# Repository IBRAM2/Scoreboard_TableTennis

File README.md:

# Tennis Scoreboard

## Simulation
The software used to perform the circuit simulations is proteus, this software its not free, so I provide a "student" version below.

Download Link: [Proteus Student Version](https://drive.google.com/drive/folders/1Nruetk5m6KCmWx57GLWE98xntiZ9FSeq?usp=drive_link)

### Installation Instructions

You need Windows OS to install proteus
1. Install the .exe, the default ***installation_path*** is: 
    > C:\Program Files (x86)\Labcenter Electronics\Proteus 8 Professional

2. On ***installation_path***/DATA/LIBRARY paste the contents of **"librerias-arduino"**

3. (Optional) On ***installation_path*** remplace Translations directory with the content of **"Paquete de idiomas"**.

### Run Simulation
1. Open **Arduino IDE**, go to File, preferences, and select verbose on compilation.

2. Compile the program, Towards the end of the terminal output, you will be able to see the path where the program was compiled
    > C:\\Users\\name\\AppData\\Local\\Temp\\arduino-sketch-38788937E004AF96E05C05CDE8CDFB3A\Scoreboard.ino.elf
    >
    Copy the path from the terminal or locate the indicated path, remember that the separators are \ and remove the " at the beginning and end.

3. Open the simulation, and double click on arduino nano, paste the path of the file .elf or .hex on **Program File:**

4. Run the simulatior by clicking on the play symbol in the bottom left corner.

*Note: Due to Arduino compiling the program into temporary files, it's possible that program execution may modify the path. However, this usually doesn't happen within the same session unless you restart the computer.*

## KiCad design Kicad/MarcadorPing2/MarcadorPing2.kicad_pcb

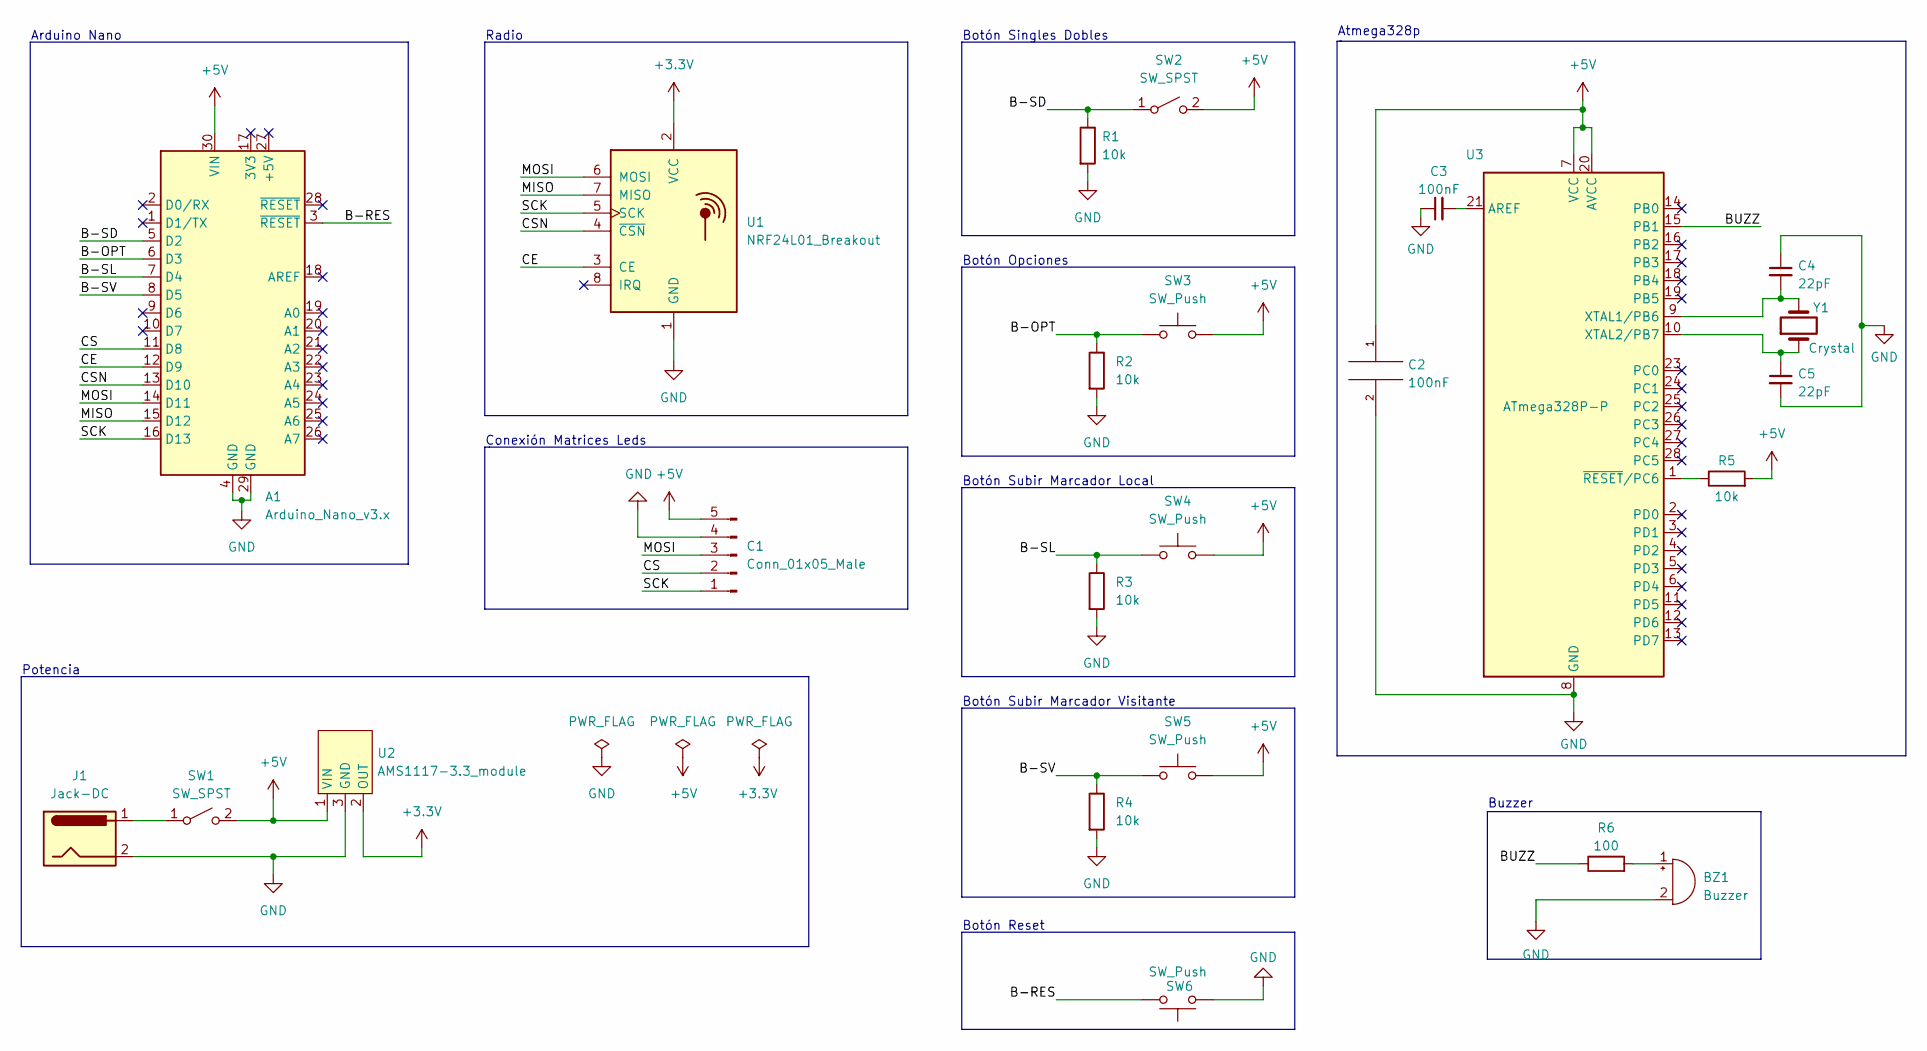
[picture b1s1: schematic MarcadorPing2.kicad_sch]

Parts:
A1: Arduino_Nano_v3.x; Arduino_Nano
BZ1: Buzzer; TerminalBlock_Phoenix_MKDS-1,5-2_1x02_P5.00mm_Horizontal
C1: Conn_01x05_Male; PinHeader_1x05_P2.54mm_Vertical
C2, C3: 100nF; C_Disc_D3.8mm_W2.6mm_P2.50mm
C4, C5: 22pF; C_1206_3216Metric_Pad1.33x1.80mm_HandSolder
J1: Jack-DC; BarrelJack_Horizontal
R1, R2, R3, R4, R5: 10k; R_Axial_DIN0207_L6.3mm_D2.5mm_P7.62mm_Horizontal
R6: 100; R_Axial_DIN0207_L6.3mm_D2.5mm_P7.62mm_Horizontal
SW1, SW2: SW_SPST; TerminalBlock_Phoenix_MKDS-1,5-2_1x02_P5.00mm_Horizontal
SW3, SW4, SW5, SW6: SW_Push; TerminalBlock_Phoenix_MKDS-1,5-2_1x02_P5.00mm_Horizontal
U1: NRF24L01_Breakout; NRF24L01
U2: AMS1117-3.3_module; AMS1117
U3: ATmega328P-P; DIP-28_W7.62mm
Y1: Crystal; Resonator-2Pin_W8.0mm_H3.5mm

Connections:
+3.3V: U1.2 (VCC), U2.2 (OUT)
+5V: A1.30 (VIN), C1.5, C2.1, R5.2, SW1.2 (B), SW2.2 (B), SW3.2, SW4.2, SW5.2, U2.1 (VIN), U3.7 (VCC), U3.20 (AVCC)
/B-OPT: A1.6 (D3), R2.1, SW3.1
/B-RES: A1.3 (~RESET), SW6.2
/B-SD: A1.5 (D2), R1.1, SW2.1 (A)
/B-SL: A1.7 (D4), R3.1, SW4.1
/B-SV: A1.8 (D5), R4.1, SW5.1
/BUZZ: R6.1, U3.15 (PB1)
/CE: A1.12 (D9), U1.3 (CE)
/CS: A1.11 (D8), C1.2
/CSN: A1.13 (D10), U1.4 (~CSN)
/MISO: A1.15 (D12), U1.7 (MISO)
/MOSI: A1.14 (D11), C1.3, U1.6 (MOSI)
/SCK: A1.16 (D13), C1.1, U1.5 (SCK)
GND: A1.4 (GND), A1.29 (GND), BZ1.2 (+), C1.4, C2.2, C3.1, C4.1, C5.2, J1.2, R1.2, R2.2, R3.2, R4.2, SW6.1, U1.1 (GND), U2.3 (GND), U3.8 (GND), U3.22 (GND)
unnamed: BZ1.1 (-), R6.2
unnamed: J1.1, SW1.1 (A)
unnamed: C3.2, U3.21 (AREF)
unnamed: C4.2, U3.9 (XTAL1/PB6), Y1.2
unnamed: C5.1, U3.10 (XTAL2/PB7), Y1.1
unnamed: R5.1, U3.1 (~RESET/PC6)

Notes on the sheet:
Radio
Conexión Matrices Leds
Buzzer
Botón Subir Marcador Local
Botón Opciones
Botón Subir Marcador Visitante
Atmega328p
Potencia
Arduino Nano
Botón Reset
Botón Singles Dobles

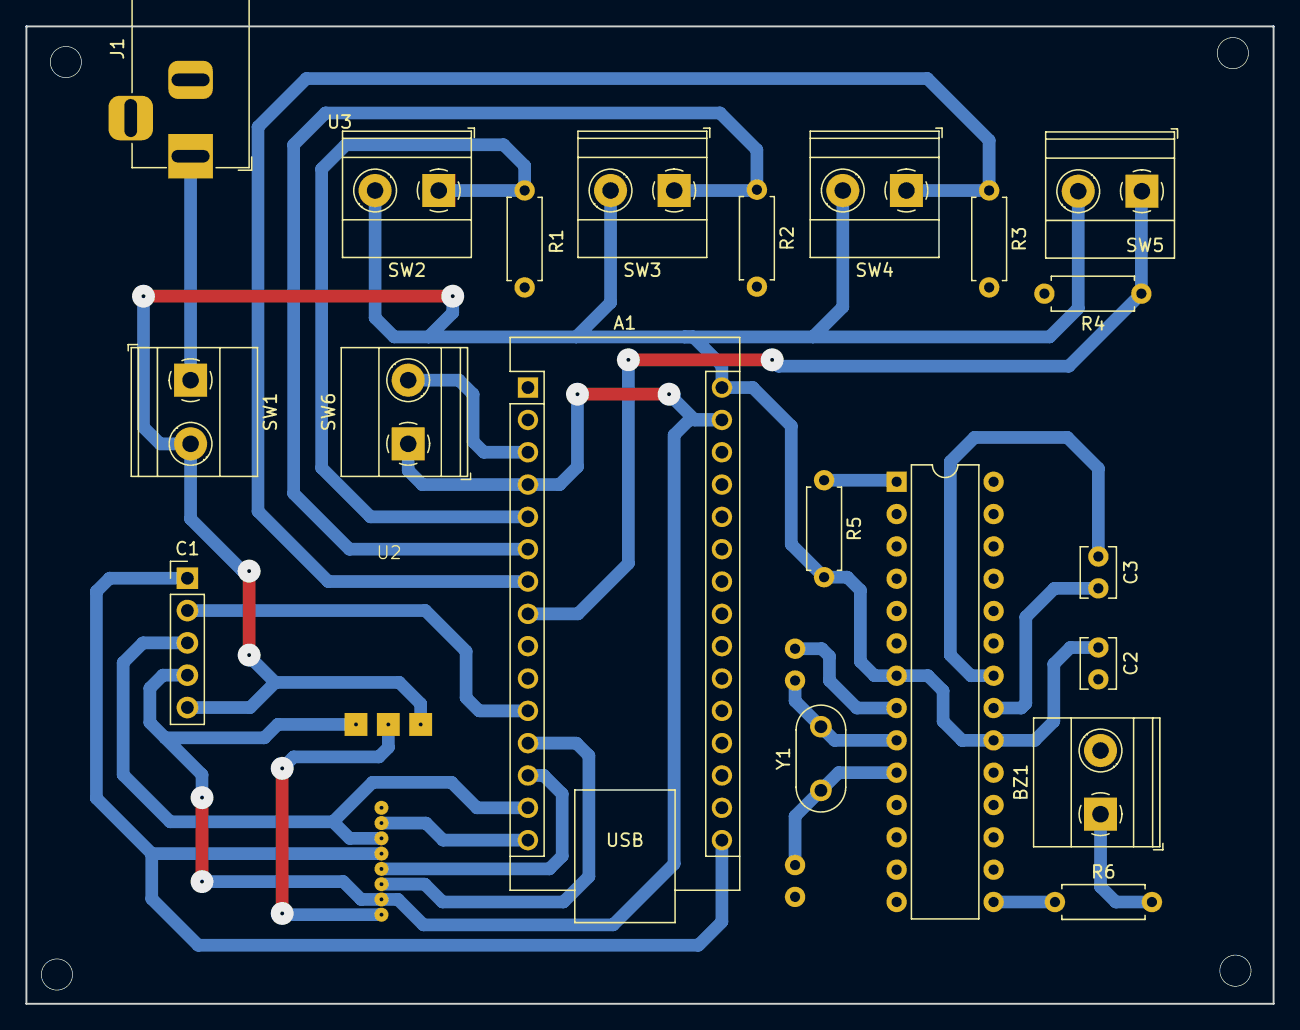
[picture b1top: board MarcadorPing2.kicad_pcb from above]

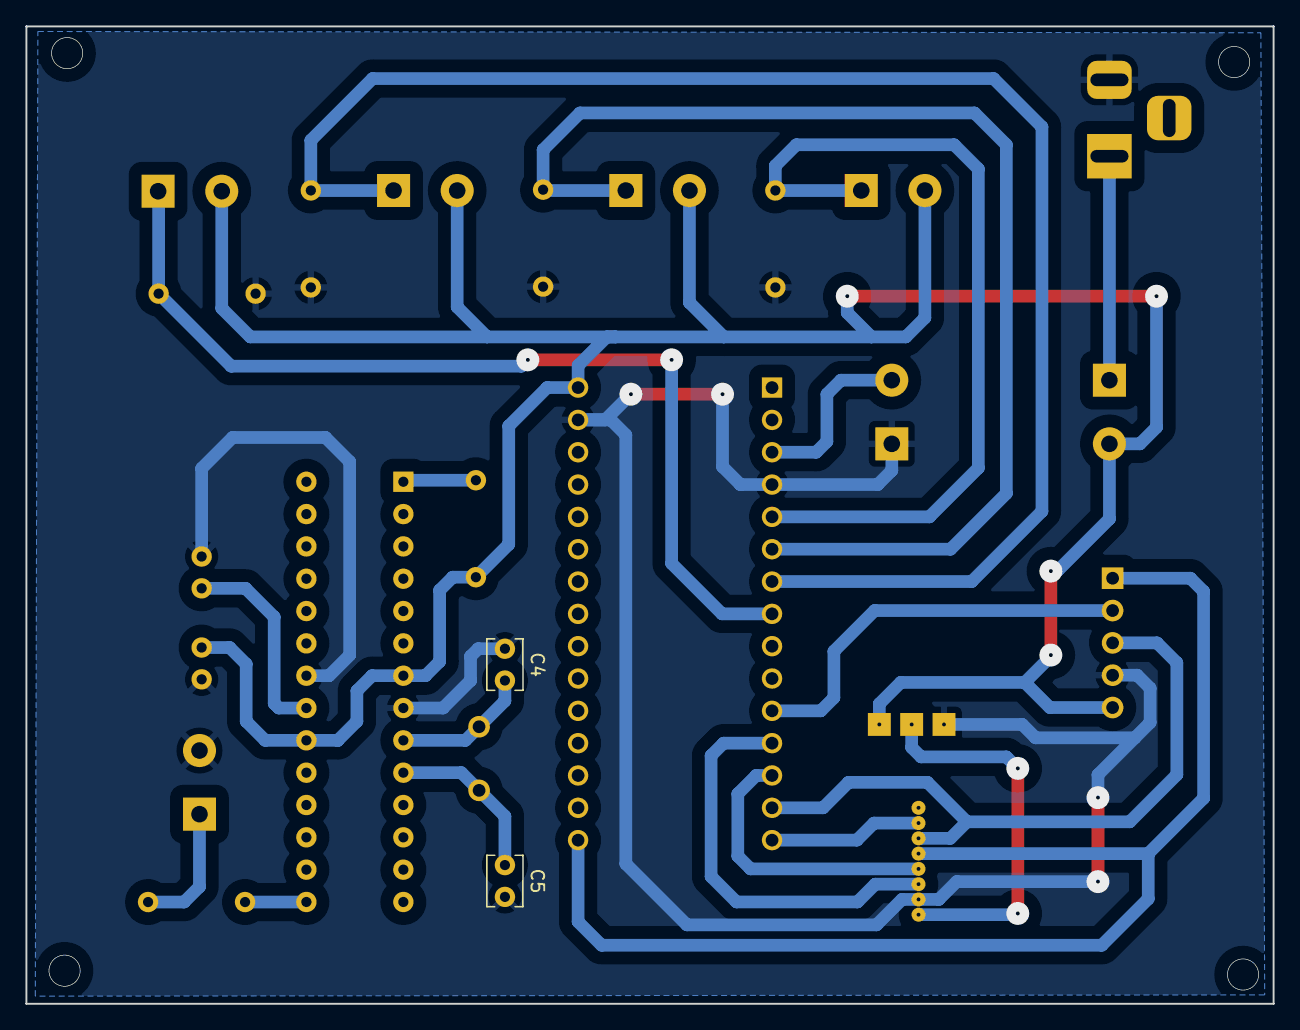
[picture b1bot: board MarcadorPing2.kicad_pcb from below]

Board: 2 copper layers, 98.0 x 76.8 mm, 24 parts (2 on the bottom side), 21 nets.

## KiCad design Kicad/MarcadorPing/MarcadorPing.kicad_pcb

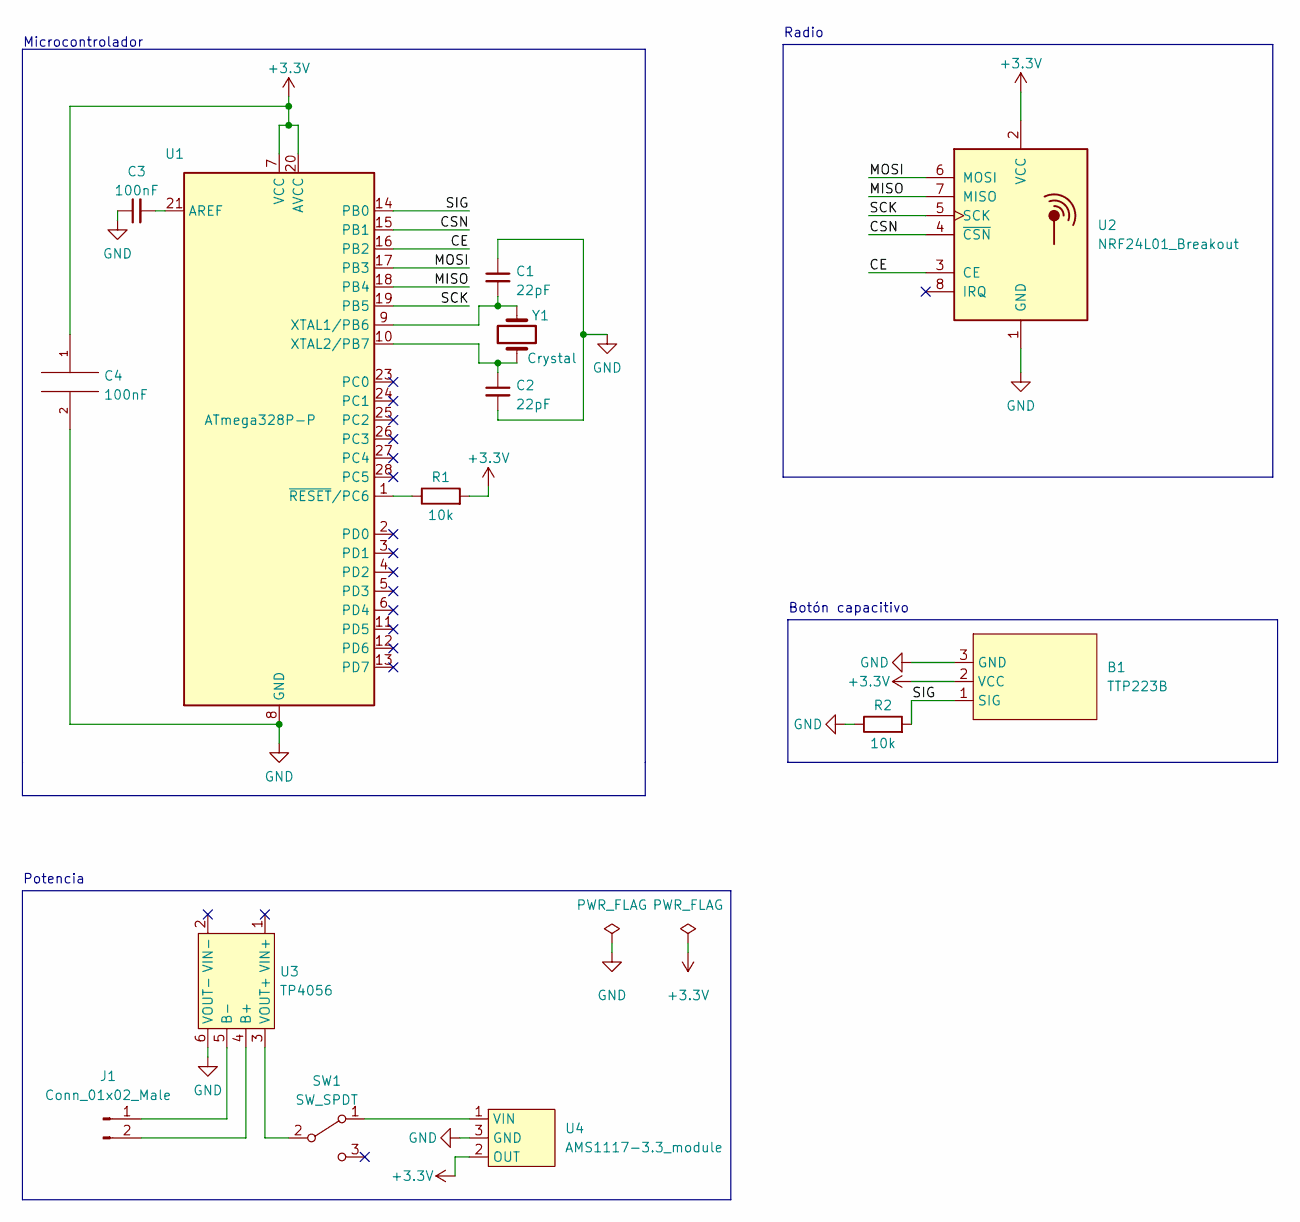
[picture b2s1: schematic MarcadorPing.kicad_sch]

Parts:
B1: TTP223B
C1, C2: 22pF; C_1206_3216Metric_Pad1.33x1.80mm_HandSolder
C3, C4: 100nF; C_Disc_D3.8mm_W2.6mm_P2.50mm
J1: Conn_01x02_Male; LiPo 502030
R1, R2: 10k; R_Axial_DIN0207_L6.3mm_D2.5mm_P7.62mm_Horizontal
SW1: SW_SPDT; PinHeader_1x03_P2.54mm_Vertical
U1: ATmega328P-P; DIP-28_W7.62mm
U2: NRF24L01_Breakout; NRF24L01
U3: TP4056
U4: AMS1117-3.3_module; AMS1117
Y1: Crystal; Resonator-2Pin_W8.0mm_H3.5mm

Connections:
+3.3V: B1.2 (VCC), C4.1, R1.2, U1.7 (VCC), U1.20 (AVCC), U2.2 (VCC), U4.2 (OUT)
/CE: U1.16 (PB2), U2.3 (CE)
/CSN: U1.15 (PB1), U2.4 (~CSN)
/MISO: U1.18 (PB4), U2.7 (MISO)
/MOSI: U1.17 (PB3), U2.6 (MOSI)
/SCK: U1.19 (PB5), U2.5 (SCK)
/SIG: B1.1 (SIG), R2.2, U1.14 (PB0)
GND: B1.3 (GND), C1.1, C2.2, C3.1, C4.2, R2.1, U1.8 (GND), U1.22 (GND), U2.1 (GND), U3.6 (VOUT-), U4.3 (GND)
unnamed: J1.1, U3.5 (B-)
unnamed: J1.2, U3.4 (B+)
unnamed: SW1.1 (A), U4.1 (VIN)
unnamed: SW1.2 (B), U3.3 (VOUT+)
unnamed: C3.2, U1.21 (AREF)
unnamed: C1.2, U1.9 (XTAL1/PB6), Y1.2
unnamed: C2.1, U1.10 (XTAL2/PB7), Y1.1
unnamed: R1.1, U1.1 (~RESET/PC6)

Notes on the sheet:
Radio
Botón capacitivo
Microcontrolador
Potencia

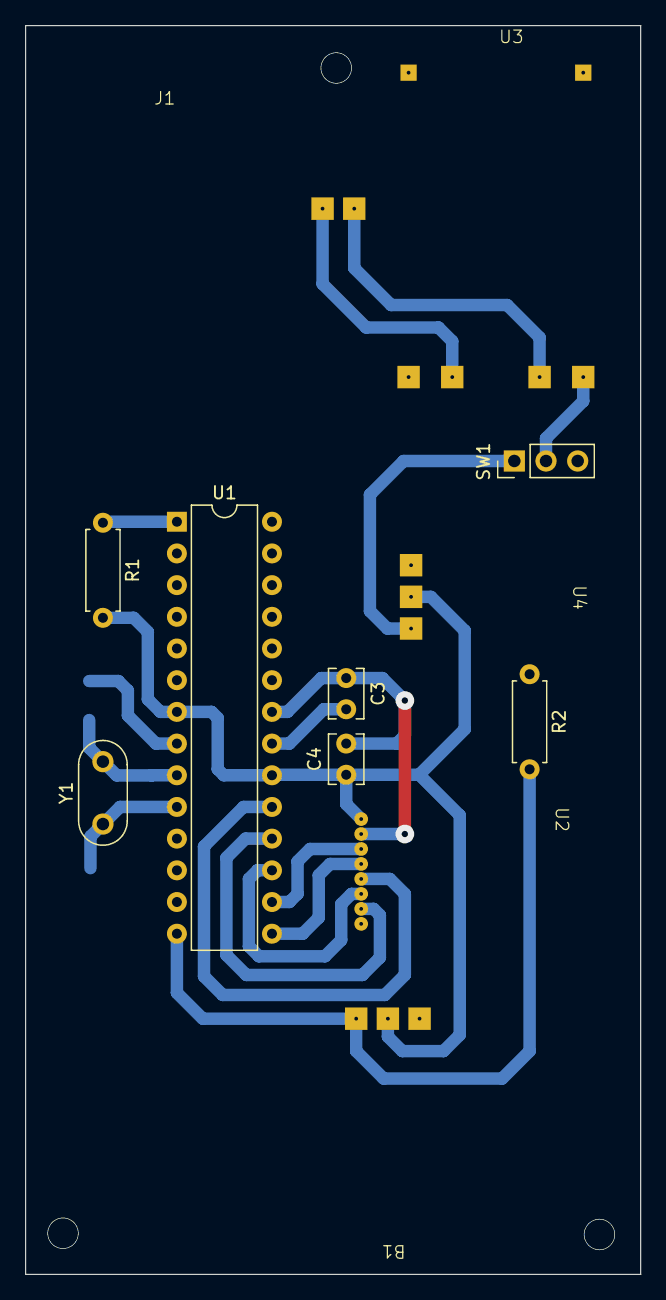
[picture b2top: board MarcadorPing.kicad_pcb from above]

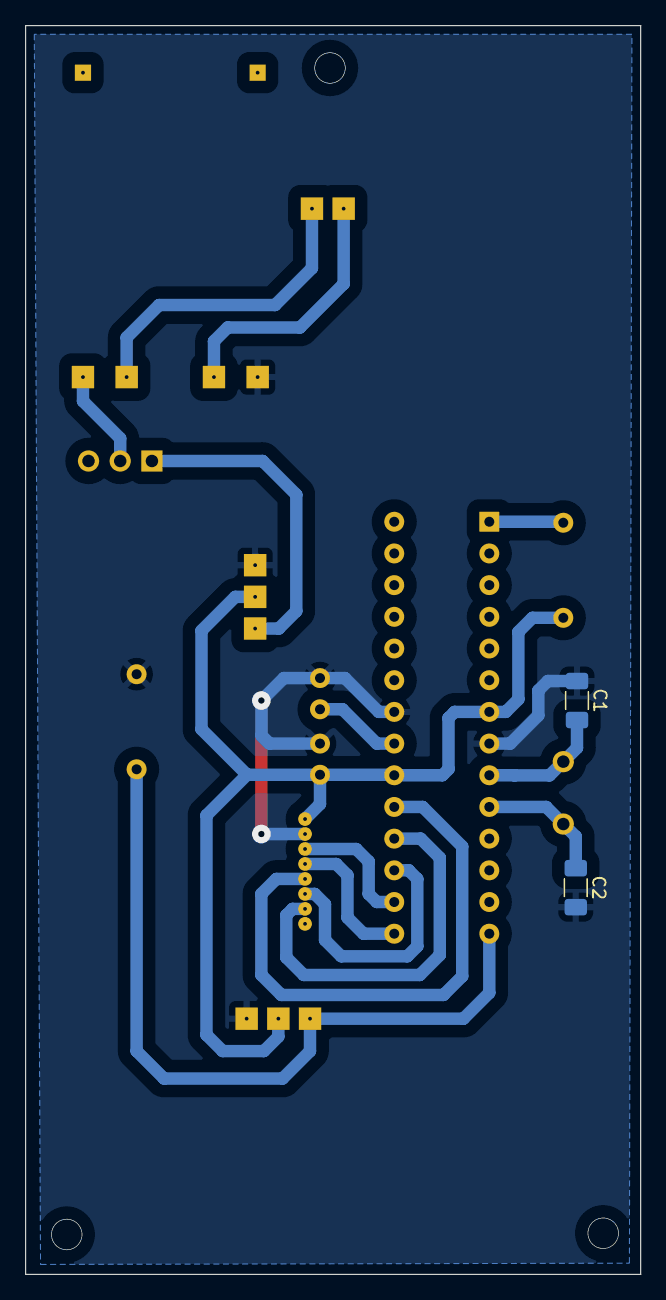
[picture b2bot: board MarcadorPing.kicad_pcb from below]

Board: 2 copper layers, 49.3 x 100.1 mm, 14 parts (2 on the bottom side), 16 nets.

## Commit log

2023-05-24 Scoreboard_first_commit
2023-05-24 libraries added
2023-05-24 library NRF24L01 updated
2023-05-24 LiPo 502030 library updated
2023-05-25 TP4056 updated
2023-05-30 Readme updated
2023-05-31 diseño pcb
2023-06-01 Puntos y Saques listo
2023-06-01 README.md renamed
2023-06-01 Mapeo de los numeros para los Sets
2023-06-02 Simulation files and instructions
2023-06-04 Implementacion de sets
2023-06-05 Implementacion_cambio_sacador
2023-06-12 Creación funcion canciones
2023-06-13 Libreria canciones
2023-06-13 Cambios placas
2023-08-16 playoffs
2023-09-17 Scorebore_completo
